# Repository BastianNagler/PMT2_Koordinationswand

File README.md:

# cWall (Interactive Coordination Wall)

cWall is an interactive, reaction-based coordination wall designed as a student project for **PMT2 (Praktikum Messtechnik 2)** during the Summer Semester 2026. 

---

## Game Concept & Play Principle
The cWall is a speed and reaction game where players must trigger randomly illuminated targets as quickly as possible within a 60-second time window.

* **Sequential Progression:** Only one box lights up at a time. The moment it is successfully pressed, the next random target activates instantly.
* **Singleplayer Mode:** The player uses the entire 32-box grid to rack up the highest score possible.
* **Multiplayer Duel Mode:** The playing field is divided into two separate, independent halves (16 boxes each) for head-to-head competition.
* **Integrated Highscores:** The system automatically tracks and saves the top 10 scores persistently.

---

## Key Features
* **ESP32-S3 Control Center:** Runs a FreeRTOS-based firmware.
* **Wireless Web Dashboard:** The ESP32-S3 acts as a Wi-Fi Access Point (SSID: `C-Wall`). By connecting to the network and navigating to `192.168.1.1`, players can view live scores, a countdown timer, game status, and the highscore board in real time. Also the game settings can be adjusted via the web interface and all the logging can be accessed for debugging and performance analysis.
* **Real-time WebSockets:** Utilizes non-blocking WebSocket communication for immediate, bi-directional data transfer between the microcontroller and web browsers.
* **Modular Sensor Boxes:** 32 individual 20x20 cm 3D-printed modular sensor boxes containing internal WS2812b NeoPixel LED strips and TTP223 capacitive touch sensors.
* **Capacitive Touch Detection:** Reliable touch response through a copper-mesh grid embedded into the acrylic faceplates, connected to low-cost, self-contained TTP223 touch chips.
* **Dedicated I/O Expansion:** Employs MCP23018 I/O expanders connected via I²C to handle the high number of digital sensor inputs while conserving ESP32 pins.
* **Robust Power Delivery:** Powered by a 300W (5V/60A) switching power supply, distributed via a star topology to prevent voltage drops when LEDs display full white.
* **Custom PCB Design:** Two-sided component PCB designed using KiCad and manufactured specifically to host the level shifters, I/O expanders, and connector terminals.
* **3D-Printed Enclosures:** All sensor boxes and the main control unit are housed in custom-designed 3D-printed enclosures for durability and aesthetics.

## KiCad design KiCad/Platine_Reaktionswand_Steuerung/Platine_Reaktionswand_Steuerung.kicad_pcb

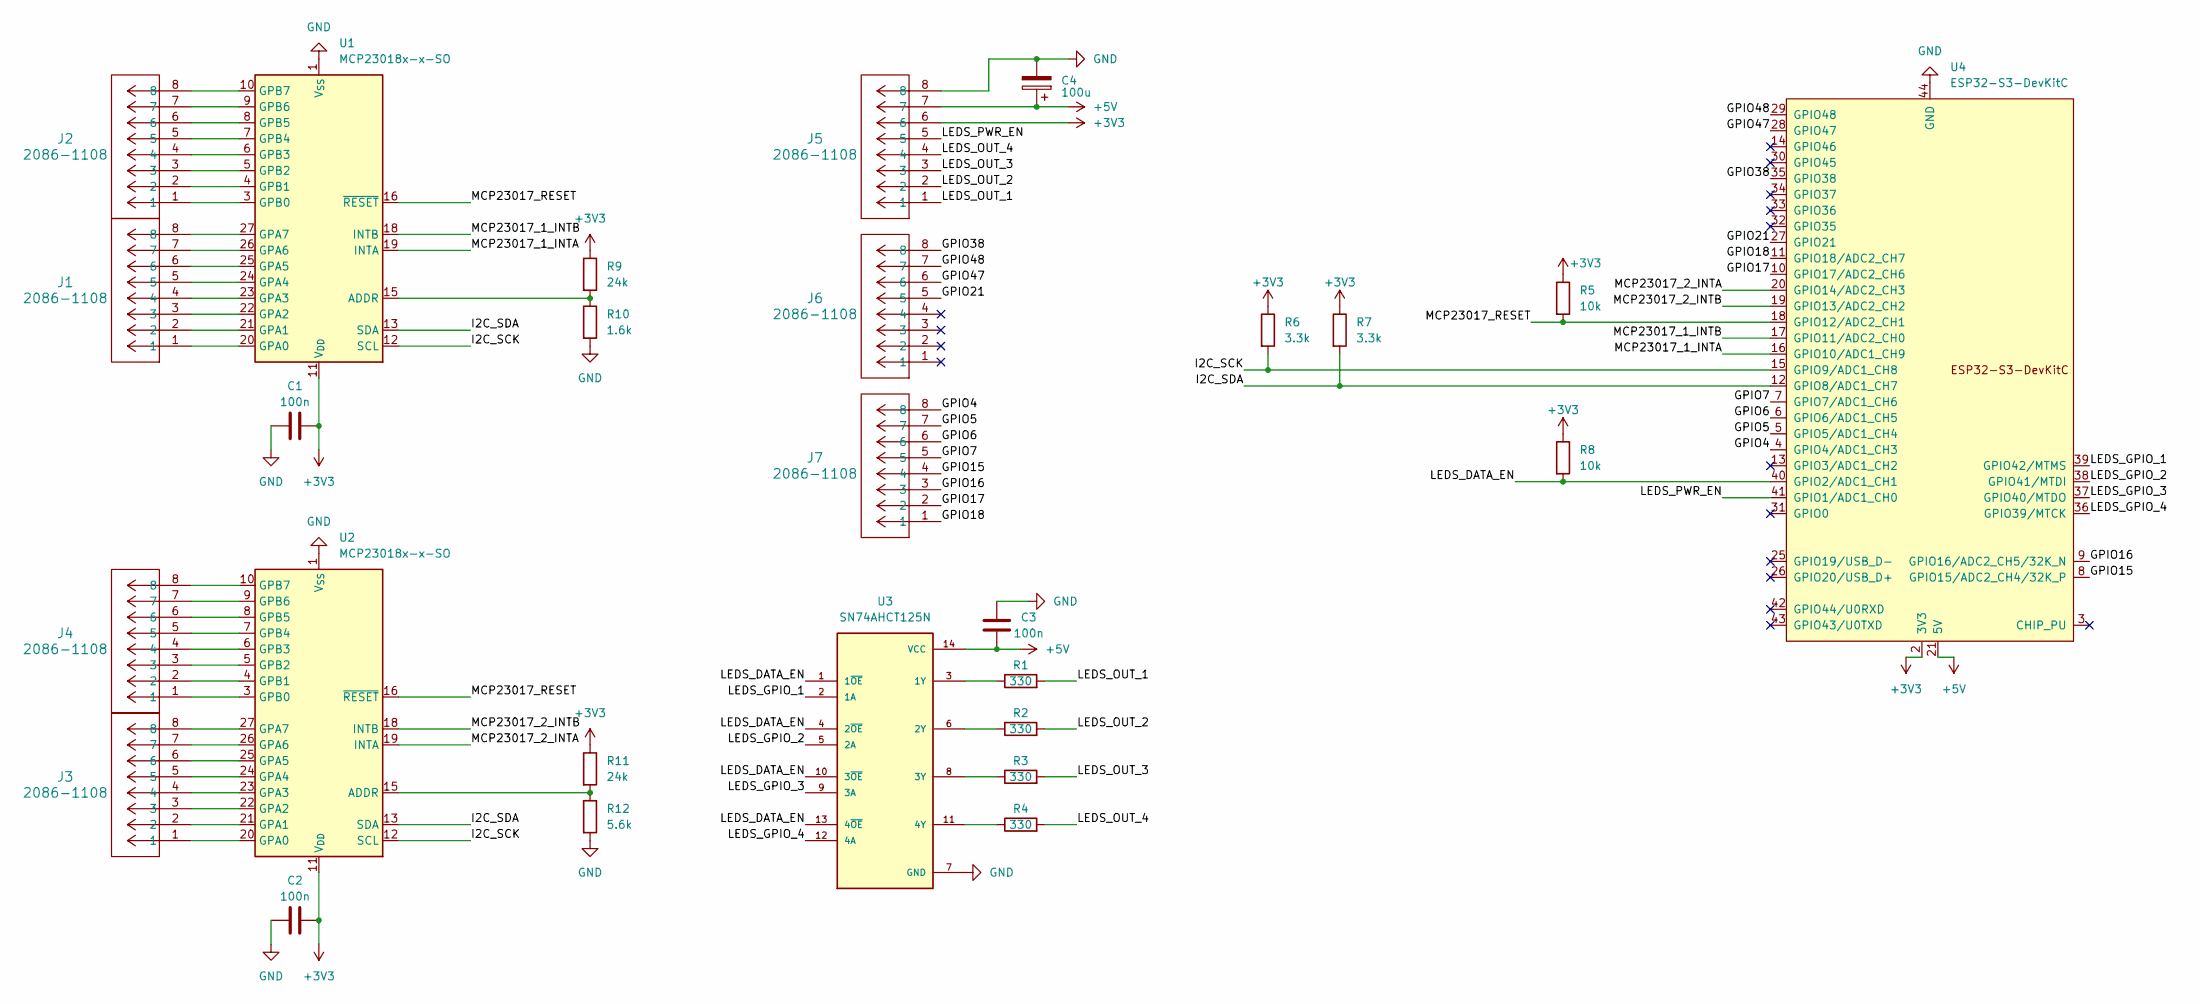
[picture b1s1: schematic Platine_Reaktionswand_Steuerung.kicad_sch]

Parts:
C1, C2, C3: 100n; C_0603_1608Metric_Pad1.08x0.95mm_HandSolder
C4: 100u; CP_Radial_D10.0mm_P5.00mm
J1, J2, J3, J4, J5, J6, J7: 2086-1108; LCSC C3309486
R1, R2, R3, R4: 330; R_0603_1608Metric_Pad0.98x0.95mm_HandSolder
R5, R8: 10k; R_0603_1608Metric_Pad0.98x0.95mm_HandSolder
R6, R7: 3.3k; R_0603_1608Metric_Pad0.98x0.95mm_HandSolder
R9, R11: 24k; R_0603_1608Metric_Pad0.98x0.95mm_HandSolder
R10: 1.6k; R_0603_1608Metric_Pad0.98x0.95mm_HandSolder
R12: 5.6k; R_0603_1608Metric_Pad0.98x0.95mm_HandSolder
U1, U2: MCP23018x-x-SO; SOIC-28W_7.5x17.9mm_P1.27mm
U3: SN74AHCT125N; SN74HCT125N; PARTREV Q; LCSC C354152
U4: ESP32-S3-DevKitC

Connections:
+3V3: C1.1, C2.1, J5.6, R5.1, R6.1, R7.1, R8.1, R9.1, R11.1, U1.11 (V_{DD}), U2.11 (V_{DD}), U4.1 (3V3), U4.2 (3V3)
+5V: C3.2, C4.1, J5.7, U3.14 (VCC), U4.21 (5V)
/GPIO4: J7.8, U4.4 (GPIO4/ADC1_CH3)
/GPIO5: J7.7, U4.5 (GPIO5/ADC1_CH4)
/GPIO6: J7.6, U4.6 (GPIO6/ADC1_CH5)
/GPIO7: J7.5, U4.7 (GPIO7/ADC1_CH6)
/GPIO15: J7.4, U4.8 (GPIO15/ADC2_CH4/32K_P)
/GPIO16: J7.3, U4.9 (GPIO16/ADC2_CH5/32K_N)
/GPIO17: J7.2, U4.10 (GPIO17/ADC2_CH6)
/GPIO18: J7.1, U4.11 (GPIO18/ADC2_CH7)
/GPIO21: J6.5, U4.27 (GPIO21)
/GPIO38: J6.8, U4.35 (GPIO38)
/GPIO47: J6.6, U4.28 (GPIO47)
/GPIO48: J6.7, U4.29 (GPIO48)
/I2C_SCK: R6.2, U1.12 (SCL), U2.12 (SCL), U4.15 (GPIO9/ADC1_CH8)
/I2C_SDA: R7.2, U1.13 (SDA), U2.13 (SDA), U4.12 (GPIO8/ADC1_CH7)
/LEDS_DATA_EN: R8.2, U3.1 (1~OE), U3.4 (2~OE), U3.10 (3~OE), U3.13 (4~OE), U4.40 (GPIO2/ADC1_CH1)
/LEDS_GPIO_1: U3.2 (1A), U4.39 (GPIO42/MTMS)
/LEDS_GPIO_2: U3.5 (2A), U4.38 (GPIO41/MTDI)
/LEDS_GPIO_3: U3.9 (3A), U4.37 (GPIO40/MTDO)
/LEDS_GPIO_4: U3.12 (4A), U4.36 (GPIO39/MTCK)
/LEDS_OUT_1: J5.1, R1.2
/LEDS_OUT_2: J5.2, R2.2
/LEDS_OUT_3: J5.3, R3.2
/LEDS_OUT_4: J5.4, R4.2
/LEDS_PWR_EN: J5.5, U4.41 (GPIO1/ADC1_CH0)
/MCP23017_1_INTA: U1.19 (INTA), U4.16 (GPIO10/ADC1_CH9)
/MCP23017_1_INTB: U1.18 (INTB), U4.17 (GPIO11/ADC2_CH0)
/MCP23017_2_INTA: U2.19 (INTA), U4.20 (GPIO14/ADC2_CH3)
/MCP23017_2_INTB: U2.18 (INTB), U4.19 (GPIO13/ADC2_CH2)
/MCP23017_RESET: R5.2, U1.16 (~RESET), U2.16 (~RESET), U4.18 (GPIO12/ADC2_CH1)
GND: C1.2, C2.2, C3.1, C4.2, J5.8, R10.2, R12.2, U1.1 (V_{SS}), U2.1 (V_{SS}), U3.7 (GND), U4.22 (GND), U4.23 (GND), U4.24 (GND), U4.44 (GND)
unnamed: R9.2, R10.1, U1.15 (ADDR)
unnamed: J1.1, U1.20 (GPA0)
unnamed: J1.2, U1.21 (GPA1)
unnamed: J1.3, U1.22 (GPA2)
unnamed: J1.4, U1.23 (GPA3)
unnamed: J1.5, U1.24 (GPA4)
unnamed: J1.6, U1.25 (GPA5)
unnamed: J1.7, U1.26 (GPA6)
unnamed: J1.8, U1.27 (GPA7)
unnamed: J2.1, U1.3 (GPB0)
unnamed: J2.2, U1.4 (GPB1)
unnamed: J2.3, U1.5 (GPB2)
unnamed: J2.4, U1.6 (GPB3)
unnamed: J2.5, U1.7 (GPB4)
unnamed: J2.6, U1.8 (GPB5)
unnamed: J2.7, U1.9 (GPB6)
unnamed: J2.8, U1.10 (GPB7)
unnamed: R11.2, R12.1, U2.15 (ADDR)
unnamed: J3.1, U2.20 (GPA0)
unnamed: J3.2, U2.21 (GPA1)
unnamed: J3.3, U2.22 (GPA2)
unnamed: J3.4, U2.23 (GPA3)
unnamed: J3.5, U2.24 (GPA4)
unnamed: J3.6, U2.25 (GPA5)
unnamed: J3.7, U2.26 (GPA6)
unnamed: J3.8, U2.27 (GPA7)
unnamed: J4.1, U2.3 (GPB0)
unnamed: J4.2, U2.4 (GPB1)
unnamed: J4.3, U2.5 (GPB2)
unnamed: J4.4, U2.6 (GPB3)
unnamed: J4.5, U2.7 (GPB4)
unnamed: J4.6, U2.8 (GPB5)
unnamed: J4.7, U2.9 (GPB6)
unnamed: J4.8, U2.10 (GPB7)
unnamed: R1.1, U3.3 (1Y)
unnamed: R2.1, U3.6 (2Y)
unnamed: R3.1, U3.8 (3Y)
unnamed: R4.1, U3.11 (4Y)

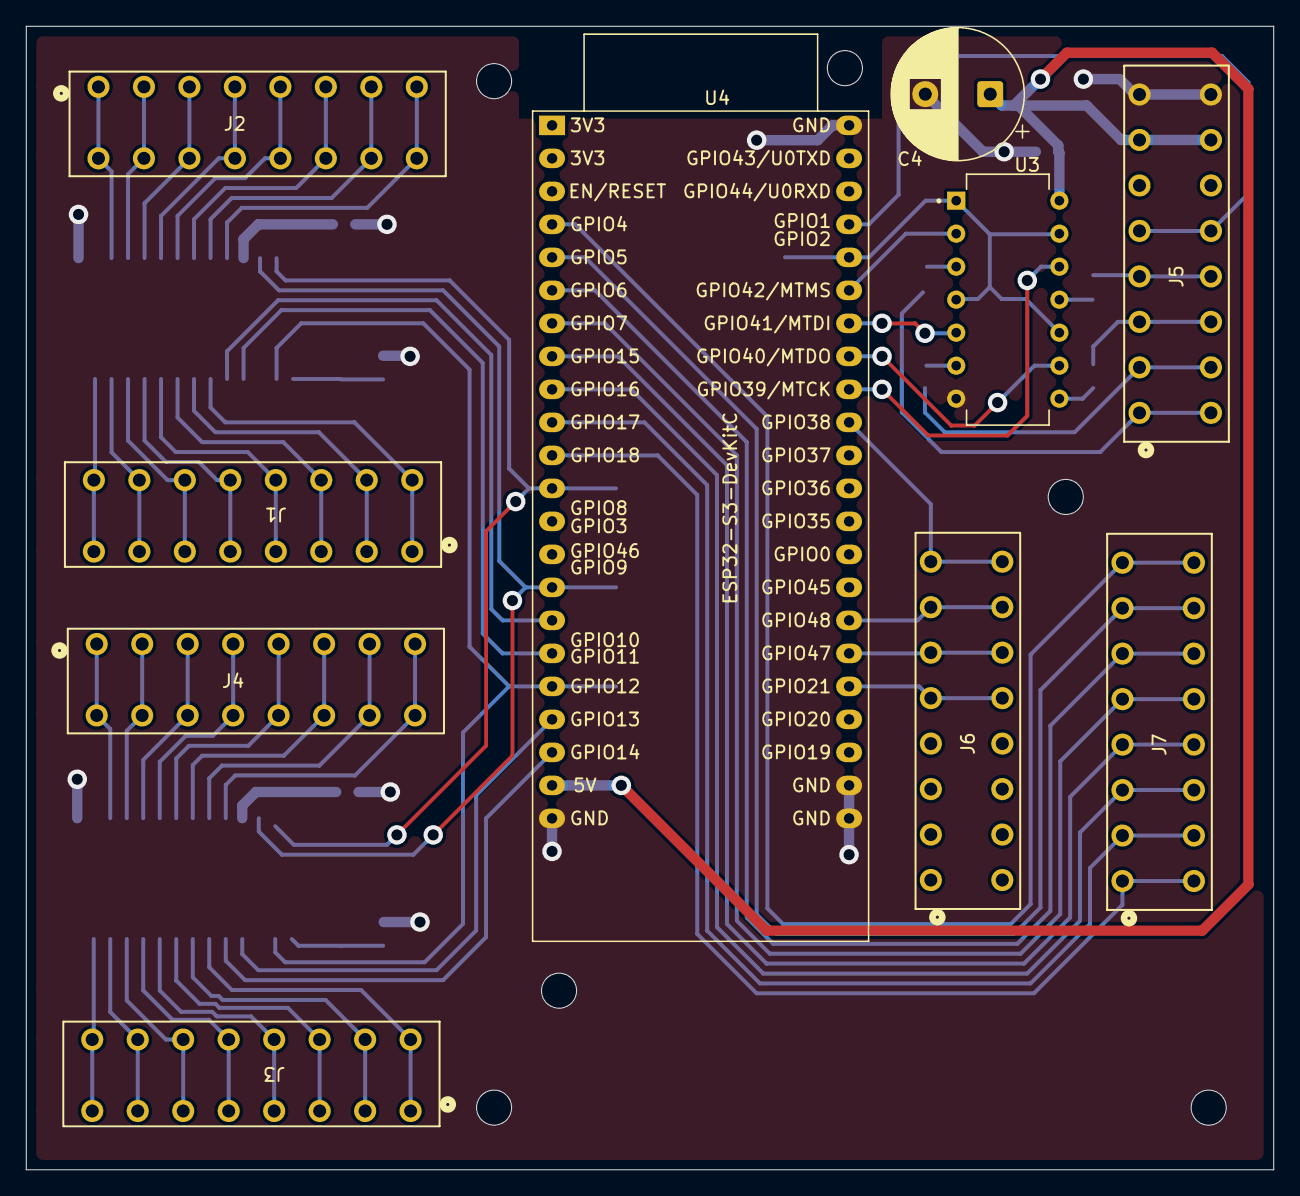
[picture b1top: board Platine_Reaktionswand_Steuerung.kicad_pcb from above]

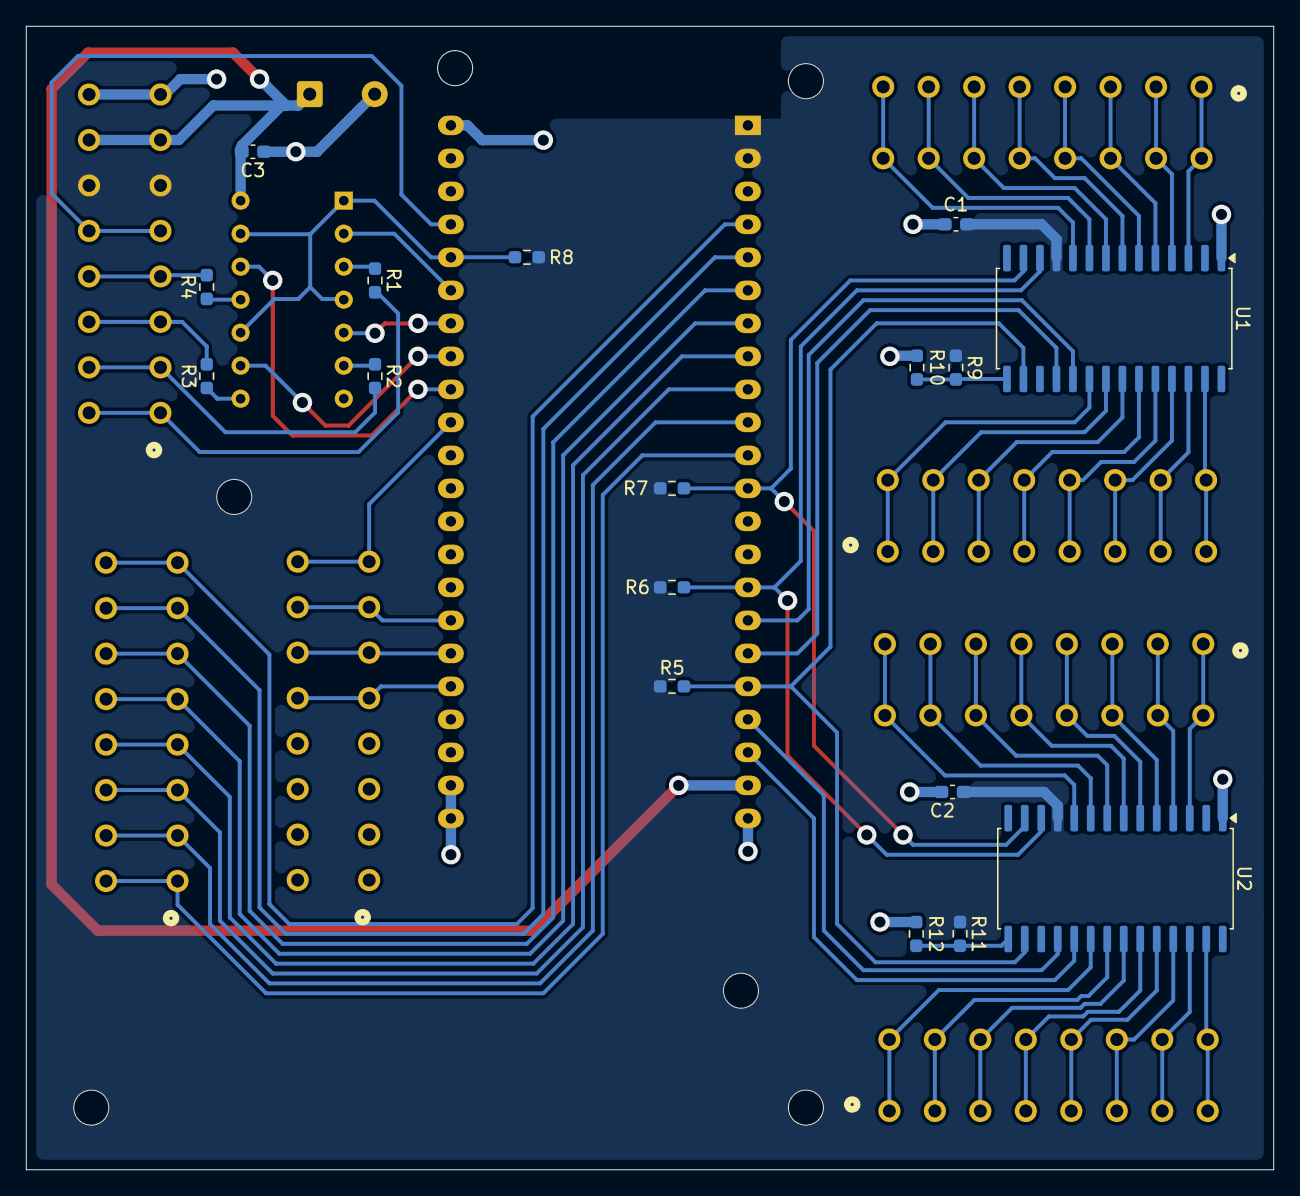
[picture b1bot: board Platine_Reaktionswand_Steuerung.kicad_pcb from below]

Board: 2 copper layers, 96.0 x 88.0 mm, 27 parts (17 on the bottom side), 70 nets.

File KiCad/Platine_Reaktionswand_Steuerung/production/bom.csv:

Designator,Footprint,Quantity,Value,LCSC Part #
"C1, C2, C3",0603,3,100n,
C4,CP_Radial_D10.0mm_P5.00mm,1,100u,
"J1, J2, J3, J4, J5, J6, J7",2086-1108,7,2086-1108,C3309486
"R1, R2, R3, R4",0603,4,330,
R10,0603,1,1.6k,
"R11, R9",0603,2,24k,
R12,0603,1,5.6k,
"R5, R8",0603,2,10k,
"R6, R7",0603,2,3.3k,
"U1, U2",SOIC-28W_7.5x17.9mm_P1.27mm,2,MCP23018x-x-SO,
U3,SN74HCT125N,1,SN74AHCT125N,C354152
U4,ESP32-S3-DevKitC,1,ESP32-S3-DevKitC,

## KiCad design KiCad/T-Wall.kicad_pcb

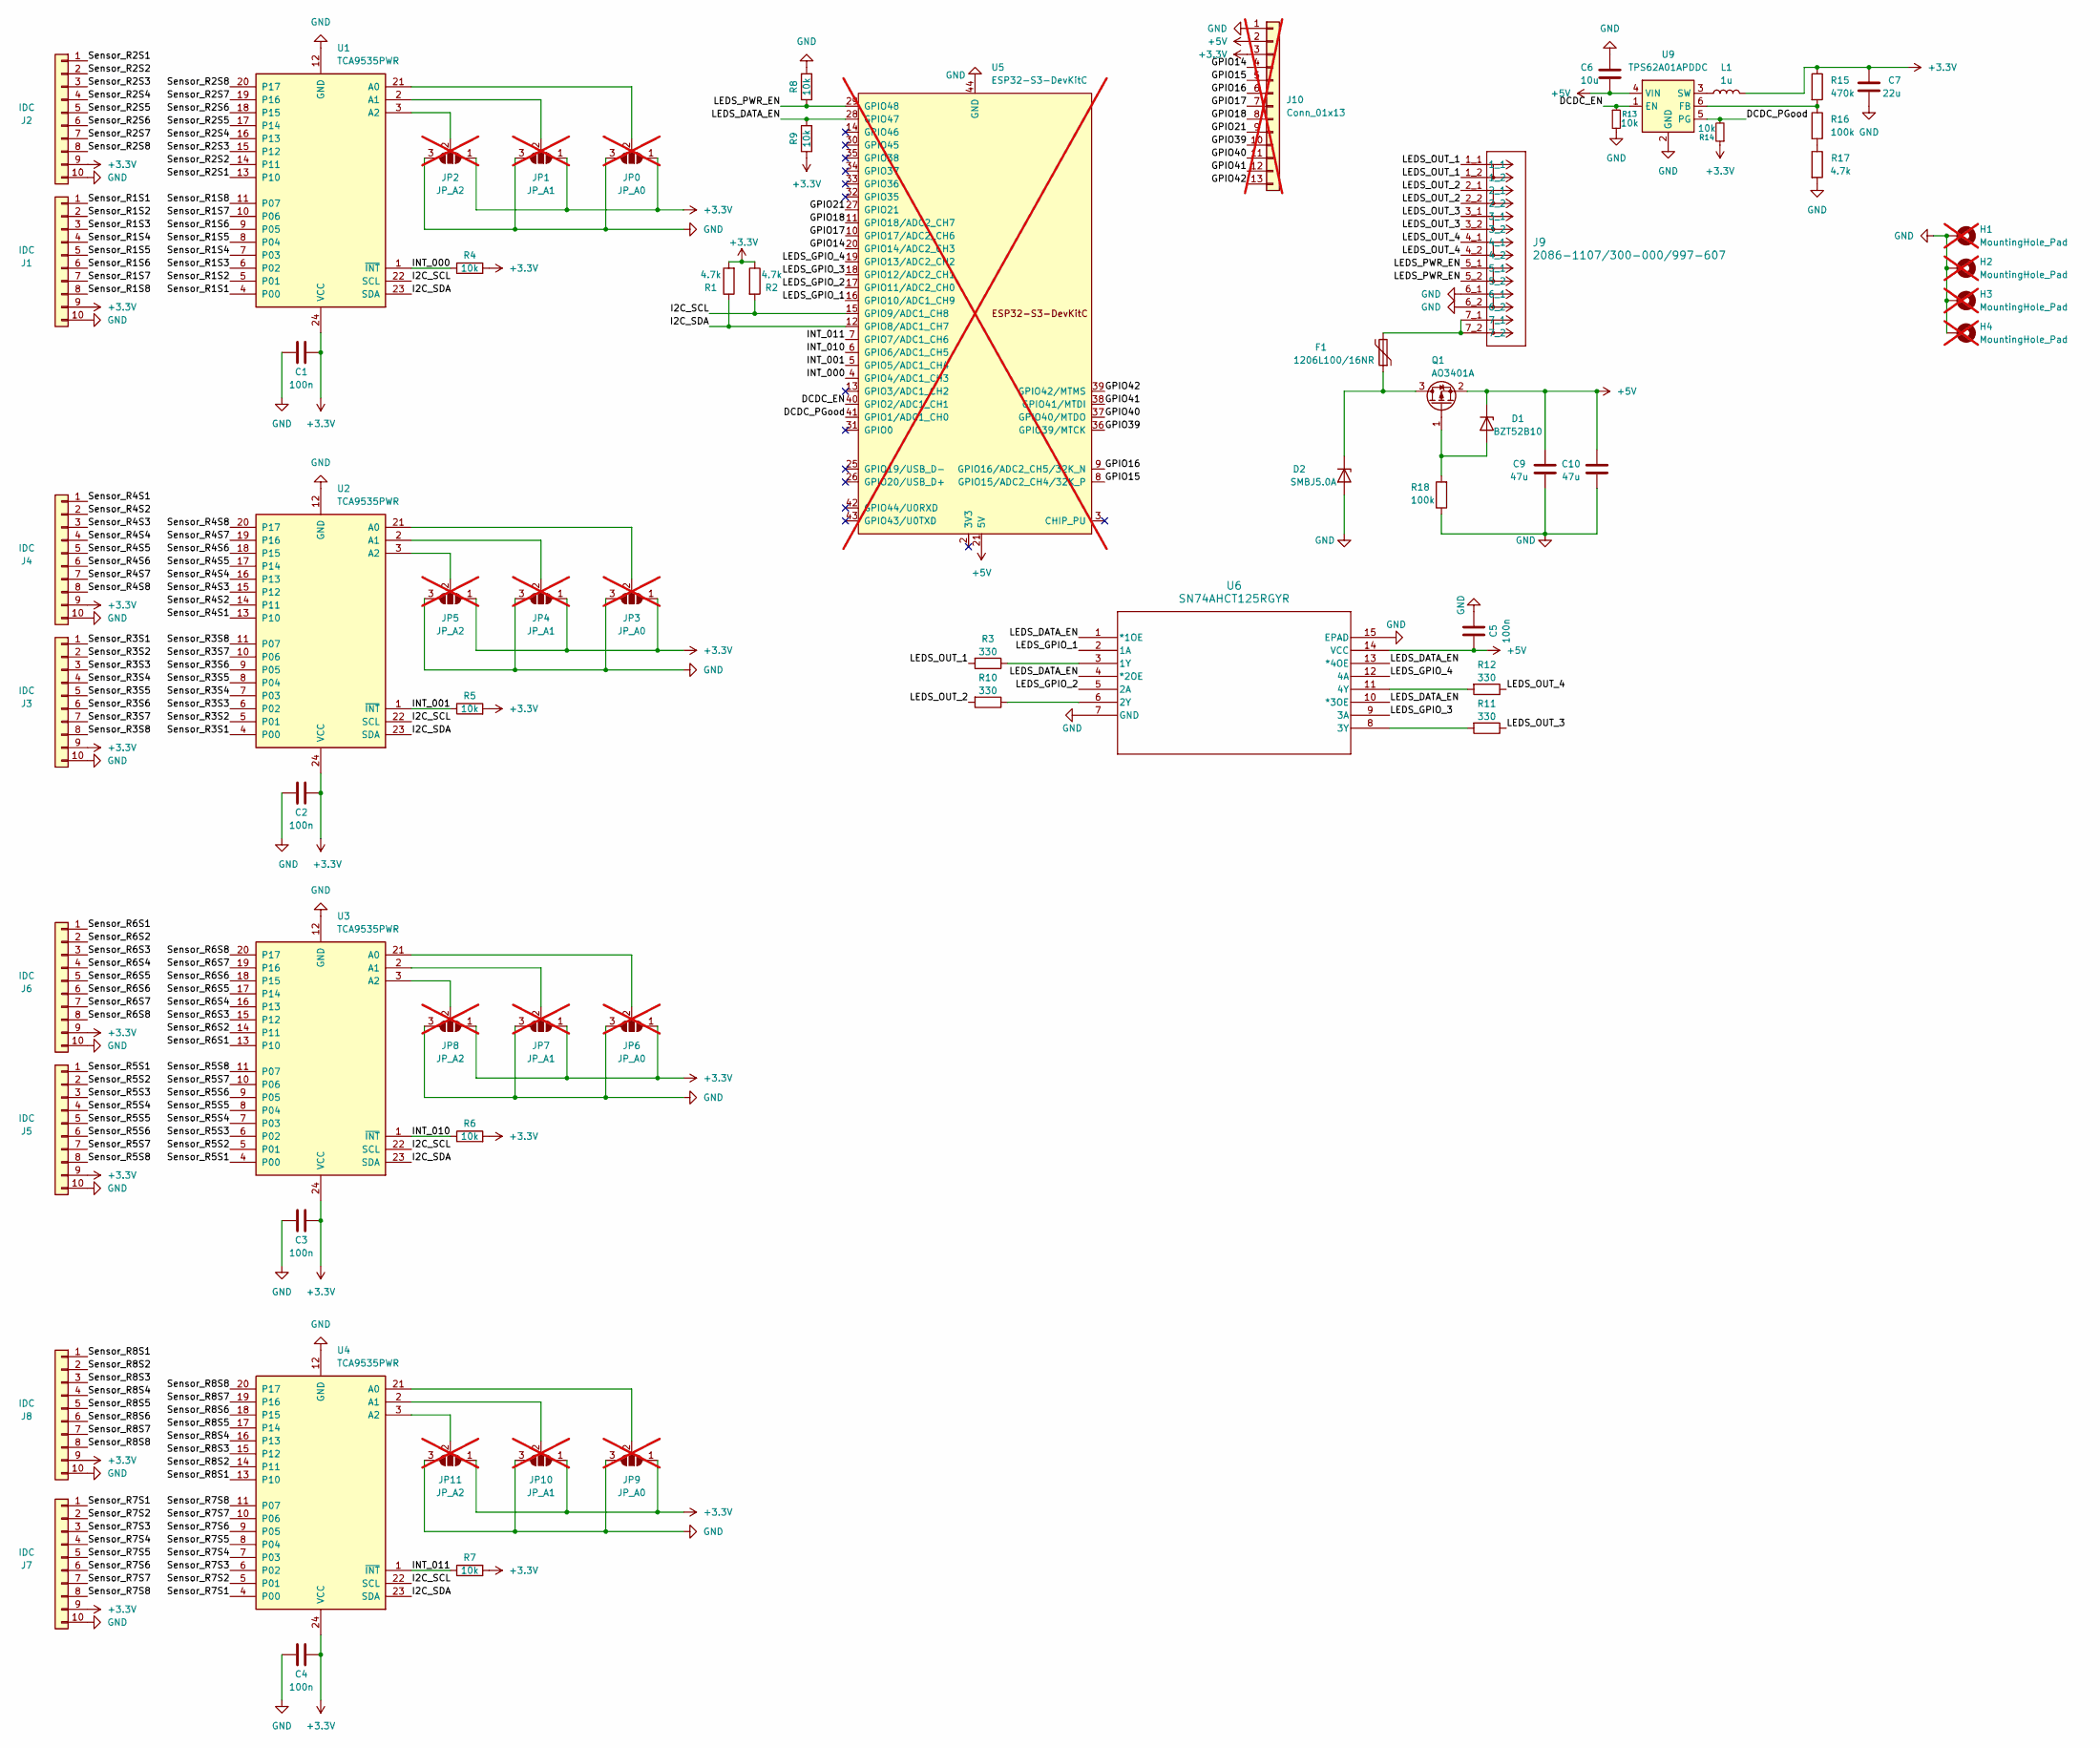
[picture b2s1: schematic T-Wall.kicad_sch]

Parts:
C1, C2, C3, C4, C5: 100n; C_0603_1608Metric_Pad1.08x0.95mm_HandSolder; LCSC C14663
C6: 10u; C_1206_3216Metric_Pad1.33x1.80mm_HandSolder; LCSC C13585
C7: 22u; C_1206_3216Metric_Pad1.33x1.80mm_HandSolder; LCSC C12891
C9, C10: 47u; C_1206_3216Metric_Pad1.33x1.80mm_HandSolder; LCSC C96123
D1: BZT52B10; D_SOD-123F; LCSC C22395568
D2: SMBJ5.0A; D_SMB_Handsoldering; LCSC C19077558
F1: 1206L100/16NR; Fuse_1206_3216Metric_Pad1.42x1.75mm_HandSolder; LCSC C7542956
H1, H2, H3, H4: MountingHole_Pad; MountingHole_3.2mm_M3_Pad_Via; not fitted
J1, J2, J3, J4, J5, J6, J7, J8: IDC; IDC-Header_2x05_P2.54mm_Vertical; LCSC C429962
J9: 2086-1107/300-000/997-607; 2086-1107_300-000_997-607; LCSC C3309486
J10: Conn_01x13; PinHeader_1x13_P2.54mm_Vertical; not fitted
JP0, JP3, JP6, JP9: JP_A0; SolderJumper-3_P1.3mm_Open_RoundedPad1.0x1.5mm; not fitted
JP1, JP4, JP7, JP10: JP_A1; SolderJumper-3_P1.3mm_Open_RoundedPad1.0x1.5mm; not fitted
JP2, JP5, JP8, JP11: JP_A2; SolderJumper-3_P1.3mm_Open_RoundedPad1.0x1.5mm; not fitted
L1: 1u; L_0805_2012Metric_Pad1.05x1.20mm_HandSolder; LCSC C6364732
Q1: AO3401A; SOT-23; LCSC C15127
R1, R2, R17: 4.7k; R_0603_1608Metric_Pad0.98x0.95mm_HandSolder; LCSC C23162
R3, R10, R11, R12: 330; R_0603_1608Metric_Pad0.98x0.95mm_HandSolder; LCSC C23138
R4, R5, R6, R7, R8, R9, R13, R14: 10k; R_0603_1608Metric_Pad0.98x0.95mm_HandSolder; LCSC C25804
R15: 470k; R_0603_1608Metric_Pad0.98x0.95mm_HandSolder; LCSC C23178
R16, R18: 100k; R_0603_1608Metric_Pad0.98x0.95mm_HandSolder; LCSC C25803
U1, U2, U3, U4: TCA9535PWR; TSSOP-24_4.4x7.8mm_P0.65mm; LCSC C130204
U5: ESP32-S3-DevKitC; not fitted
U6: SN74AHCT125RGYR; LCSC C2675532
U9: TPS62A01APDDC; SOT-23-6; LCSC C41730179

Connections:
+3.3V: C1.1, C2.1, C3.1, C4.1, C7.2, J1.9, J2.9, J3.9, J4.9, J5.9, J6.9, J7.9, J8.9, J10.3, JP0.1 (A), JP1.1 (A), JP2.1 (A), JP3.1 (A), JP4.1 (A), JP5.1 (A), JP6.1 (A), JP7.1 (A), JP8.1 (A), JP9.1 (A), JP10.1 (A), JP11.1 (A), L1.2, R1.2, R2.1, R4.2, R5.2, R6.2, R7.2, R9.1, R14.1, R15.1, U1.24 (VCC), U2.24 (VCC), U3.24 (VCC), U4.24 (VCC)
+5V: C5.2, C6.2, C9.2, C10.2, D1.1 (K), J10.2, Q1.2 (S), U5.21 (5V), U6.14 (VCC), U9.4 (VIN)
/DCDC_EN: R13.1, U5.40 (GPIO2/ADC1_CH1), U9.1 (EN)
/DCDC_PGood: R14.2, U5.41 (GPIO1/ADC1_CH0), U9.5 (PG)
/GPIO14: J10.4, U5.20 (GPIO14/ADC2_CH3)
/GPIO15: J10.5, U5.8 (GPIO15/ADC2_CH4/32K_P)
/GPIO16: J10.6, U5.9 (GPIO16/ADC2_CH5/32K_N)
/GPIO17: J10.7, U5.10 (GPIO17/ADC2_CH6)
/GPIO18: J10.8, U5.11 (GPIO18/ADC2_CH7)
/GPIO21: J10.9, U5.27 (GPIO21)
/GPIO39: J10.10, U5.36 (GPIO39/MTCK)
/GPIO40: J10.11, U5.37 (GPIO40/MTDO)
/GPIO41: J10.12, U5.38 (GPIO41/MTDI)
/GPIO42: J10.13, U5.39 (GPIO42/MTMS)
/I2C_SCL: R2.2, U1.22 (SCL), U2.22 (SCL), U3.22 (SCL), U4.22 (SCL), U5.15 (GPIO9/ADC1_CH8)
/I2C_SDA: R1.1, U1.23 (SDA), U2.23 (SDA), U3.23 (SDA), U4.23 (SDA), U5.12 (GPIO8/ADC1_CH7)
/INT_000: R4.1, U1.1 (~INT), U5.4 (GPIO4/ADC1_CH3)
/INT_001: R5.1, U2.1 (~INT), U5.5 (GPIO5/ADC1_CH4)
/INT_010: R6.1, U3.1 (~INT), U5.6 (GPIO6/ADC1_CH5)
/INT_011: R7.1, U4.1 (~INT), U5.7 (GPIO7/ADC1_CH6)
/LEDS_DATA_EN: R9.2, U5.28 (GPIO47), U6.1 (*1OE), U6.4 (*2OE), U6.10 (*3OE), U6.13 (*4OE)
/LEDS_GPIO_1: U5.16 (GPIO10/ADC1_CH9), U6.2 (1A)
/LEDS_GPIO_2: U5.17 (GPIO11/ADC2_CH0), U6.5 (2A)
/LEDS_GPIO_3: U5.18 (GPIO12/ADC2_CH1), U6.9 (3A)
/LEDS_GPIO_4: U5.19 (GPIO13/ADC2_CH2), U6.12 (4A)
/LEDS_OUT_1: J9.1_1, J9.1_2, R3.2
/LEDS_OUT_2: J9.2_1, J9.2_2, R10.2
/LEDS_OUT_3: J9.3_1, J9.3_2, R11.1
/LEDS_OUT_4: J9.4_1, J9.4_2, R12.1
/LEDS_PWR_EN: J9.5_1, J9.5_2, R8.1, U5.29 (GPIO48)
/Sensor_R1S1: J1.1, U1.4 (P00)
/Sensor_R1S2: J1.2, U1.5 (P01)
/Sensor_R1S3: J1.3, U1.6 (P02)
/Sensor_R1S4: J1.4, U1.7 (P03)
/Sensor_R1S5: J1.5, U1.8 (P04)
/Sensor_R1S6: J1.6, U1.9 (P05)
/Sensor_R1S7: J1.7, U1.10 (P06)
/Sensor_R1S8: J1.8, U1.11 (P07)
/Sensor_R2S1: J2.1, U1.13 (P10)
/Sensor_R2S2: J2.2, U1.14 (P11)
/Sensor_R2S3: J2.3, U1.15 (P12)
/Sensor_R2S4: J2.4, U1.16 (P13)
/Sensor_R2S5: J2.5, U1.17 (P14)
/Sensor_R2S6: J2.6, U1.18 (P15)
/Sensor_R2S7: J2.7, U1.19 (P16)
/Sensor_R2S8: J2.8, U1.20 (P17)
/Sensor_R3S1: J3.1, U2.4 (P00)
/Sensor_R3S2: J3.2, U2.5 (P01)
/Sensor_R3S3: J3.3, U2.6 (P02)
/Sensor_R3S4: J3.4, U2.7 (P03)
/Sensor_R3S5: J3.5, U2.8 (P04)
/Sensor_R3S6: J3.6, U2.9 (P05)
/Sensor_R3S7: J3.7, U2.10 (P06)
/Sensor_R3S8: J3.8, U2.11 (P07)
/Sensor_R4S1: J4.1, U2.13 (P10)
/Sensor_R4S2: J4.2, U2.14 (P11)
/Sensor_R4S3: J4.3, U2.15 (P12)
/Sensor_R4S4: J4.4, U2.16 (P13)
/Sensor_R4S5: J4.5, U2.17 (P14)
/Sensor_R4S6: J4.6, U2.18 (P15)
/Sensor_R4S7: J4.7, U2.19 (P16)
/Sensor_R4S8: J4.8, U2.20 (P17)
/Sensor_R5S1: J5.1, U3.4 (P00)
/Sensor_R5S2: J5.2, U3.5 (P01)
/Sensor_R5S3: J5.3, U3.6 (P02)
/Sensor_R5S4: J5.4, U3.7 (P03)
/Sensor_R5S5: J5.5, U3.8 (P04)
/Sensor_R5S6: J5.6, U3.9 (P05)
/Sensor_R5S7: J5.7, U3.10 (P06)
/Sensor_R5S8: J5.8, U3.11 (P07)
/Sensor_R6S1: J6.1, U3.13 (P10)
/Sensor_R6S2: J6.2, U3.14 (P11)
/Sensor_R6S3: J6.3, U3.15 (P12)
/Sensor_R6S4: J6.4, U3.16 (P13)
/Sensor_R6S5: J6.5, U3.17 (P14)
/Sensor_R6S6: J6.6, U3.18 (P15)
/Sensor_R6S7: J6.7, U3.19 (P16)
/Sensor_R6S8: J6.8, U3.20 (P17)
/Sensor_R7S1: J7.1, U4.4 (P00)
/Sensor_R7S2: J7.2, U4.5 (P01)
/Sensor_R7S3: J7.3, U4.6 (P02)
/Sensor_R7S4: J7.4, U4.7 (P03)
/Sensor_R7S5: J7.5, U4.8 (P04)
/Sensor_R7S6: J7.6, U4.9 (P05)
/Sensor_R7S7: J7.7, U4.10 (P06)
/Sensor_R7S8: J7.8, U4.11 (P07)
/Sensor_R8S1: J8.1, U4.13 (P10)
/Sensor_R8S2: J8.2, U4.14 (P11)
/Sensor_R8S3: J8.3, U4.15 (P12)
/Sensor_R8S4: J8.4, U4.16 (P13)
/Sensor_R8S5: J8.5, U4.17 (P14)
/Sensor_R8S6: J8.6, U4.18 (P15)
/Sensor_R8S7: J8.7, U4.19 (P16)
/Sensor_R8S8: J8.8, U4.20 (P17)
GND: C1.2, C2.2, C3.2, C4.2, C5.1, C6.1, C7.1, C9.1, C10.1, D2.2 (A), H1.1 (1_1), H2.1 (1_1), H3.1 (1_1), H4.1 (1_1), J1.10, J2.10, J3.10, J4.10, J5.10, J6.10, J7.10, J8.10, J9.6_1, J9.6_2, J10.1, JP0.3 (B), JP1.3 (B), JP2.3 (B), JP3.3 (B), JP4.3 (B), JP5.3 (B), JP6.3 (B), JP7.3 (B), JP8.3 (B), JP9.3 (B), JP10.3 (B), JP11.3 (B), R8.2, R13.2, R17.2, R18.1, U1.12 (GND), U2.12 (GND), U3.12 (GND), U4.12 (GND), U5.22 (GND), U5.23 (GND), U5.24 (GND), U5.44 (GND), U6.7 (GND), U6.15 (EPAD), U9.2 (GND)
unnamed: D1.2 (A), Q1.1 (G), R18.2
unnamed: D2.1 (K), F1.1, Q1.3 (D)
unnamed: F1.2, J9.7_1, J9.7_2
unnamed: JP0.2 (C), U1.21 (A0)
unnamed: JP1.2 (C), U1.2 (A1)
unnamed: JP2.2 (C), U1.3 (A2)
unnamed: JP3.2 (C), U2.21 (A0)
unnamed: JP4.2 (C), U2.2 (A1)
unnamed: JP5.2 (C), U2.3 (A2)
unnamed: JP6.2 (C), U3.21 (A0)
unnamed: JP7.2 (C), U3.2 (A1)
unnamed: JP8.2 (C), U3.3 (A2)
unnamed: JP9.2 (C), U4.21 (A0)
unnamed: JP10.2 (C), U4.2 (A1)
unnamed: JP11.2 (C), U4.3 (A2)
unnamed: R16.2, R17.1
unnamed: R3.1, U6.3 (1Y)
unnamed: R10.1, U6.6 (2Y)
unnamed: R11.2, U6.8 (3Y)
unnamed: R12.2, U6.11 (4Y)
unnamed: R15.2, R16.1, U9.6 (FB)
unnamed: L1.1, U9.3 (SW)

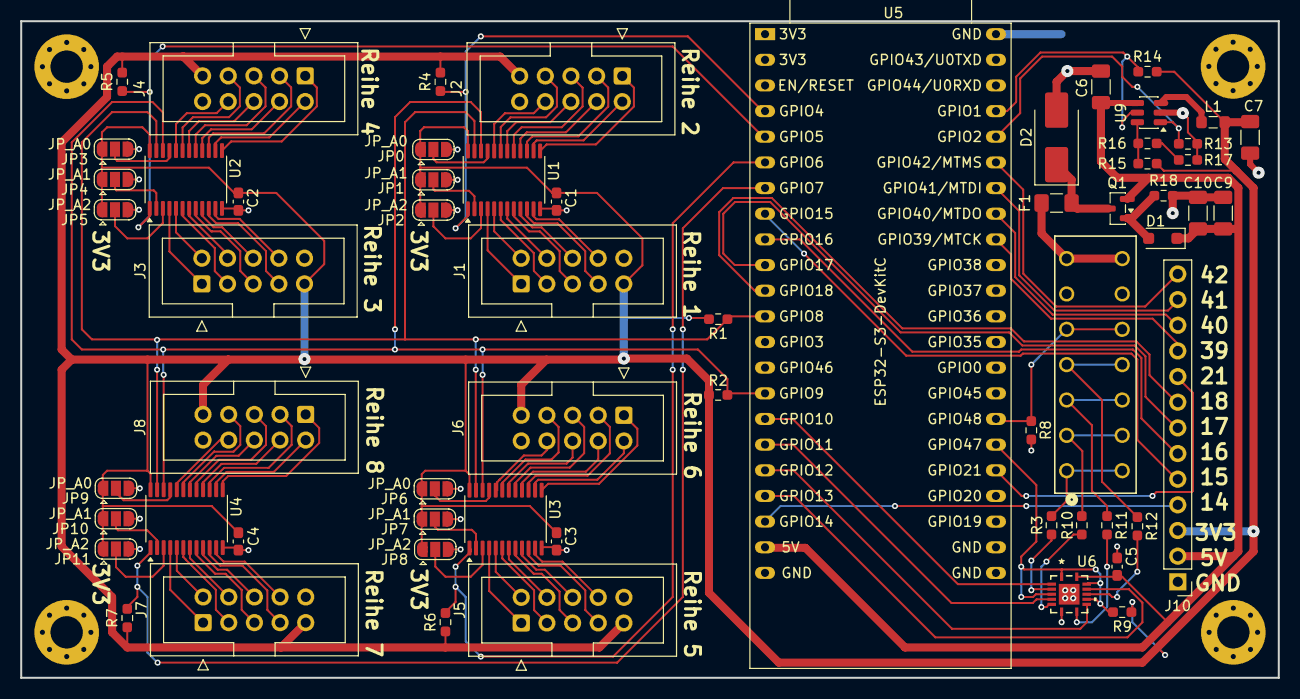
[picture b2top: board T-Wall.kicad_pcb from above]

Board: 2 copper layers, 124.5 x 65.0 mm, 65 parts (0 on the bottom side), 117 nets.

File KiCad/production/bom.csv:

Designator,Footprint,Quantity,Value,LCSC Part #
"C1, C2, C3, C4, C5",0603,5,100n,C14663
"C10, C9",1206,2,47u,C96123
C6,1206,1,10u,C13585
C7,1206,1,22u,C12891
D1,D_SOD-123F,1,BZT52B10,C22395568
D2,D_SMB_Handsoldering,1,SMBJ5.0A,C19077558
F1,1206,1,1206L100/16NR,C7542956
"J1, J2, J3, J4, J5, J6, J7, J8",IDC-Header_2x05_P2.54mm_Vertical,8,IDC,C429962
J9,2086-1107_300-000_997-607,1,2086-1107/300-000/997-607,C3309486
L1,0805,1,1u,C6364732
Q1,SOT-23,1,AO3401A,C15127
"R1, R17, R2",0603,3,4.7k,C23162
"R10, R11, R12, R3",0603,4,330,C23138
"R13, R14, R4, R5, R6, R7, R8, R9",0603,8,10k,C25804
R15,0603,1,470k,C23178
"R16, R18",0603,2,100k,C25803
"U1, U2, U3, U4",TSSOP-24_4.4x7.8mm_P0.65mm,4,TCA9535PWR,C130204
U6,SN74AHCT125RGYR,1,SN74AHCT125RGYR,C2675532
U9,SOT-23-6,1,TPS62A01APDDC,C41730179

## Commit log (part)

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2026-03-06 Added support for Fields in LED_Driver and added RGB_Color class
2026-03-06 Changed TCA9555_Driver to be universally usable
2026-03-09 minor QOL changes
2026-03-09 fixed correct init
2026-03-09 Added working Project for 1st Prototype
2026-03-09 updated LED_Driver to use allocated array instead of std::vector
2026-03-11 Fixed minor issue in LED_Driver (wrong constant used in set_led_in_field)
2026-03-11 EOD 11.03
2026-03-12 PCB Revision 1
2026-03-12 PCB Revision 2
2026-03-13 EOD 1303
2026-03-13 added KiCad libraries to repo
2026-03-16 changed KiCad libraries to project-specific libraries
2026-03-16 added ESP32 Software to repo
2026-03-17 just some BWL things...
2026-03-18 Finished BWL-rebuild
2026-03-29 added 3D-print files for a single box
2026-03-29 added cmake-build directory to gitignore
2026-03-29 fixed correct define for FastLED to use I2S
2026-03-29 fixed false fix for FastLED to use I2S (testing is important)
2026-03-29 added 100 nF capacitor for the level-shifter
2026-03-29 PCB QOL: changed sizes to 0603 and moved vias away from pads
2026-03-30 irgendwas schaltplan
2026-03-30 PCB: routed unused GPIOs to Pins
2026-04-06 deleted config for non-WS2812b LEDs
2026-04-07 PCB: corrected WAGO footprint
2026-04-09 PCB: added fuse and reverse-polarity-protection
2026-04-09 changed colors to cyan and yellow
2026-04-11 PCB: overvoltage-protection and optimized routing
2026-04-11 PCB: upgraded KiCad to 10.0.1
2026-04-12 PCB: finished for purchase at JLCPCB
2026-04-16 added MCP23017 support to ESP program
2026-04-18 cleared warning for MCP23017 driver
2026-04-19 added game Logic in main (todo: new class and file)
2026-04-19 added color GRAY
2026-04-19 added led-driver as a HAL
2026-04-19 added bool ispressed(intdex)
2026-04-19 changed pin-config for use with test-breadboard
2026-04-20 changed startgame()
2026-04-20 changed game logic (State machine)
2026-04-20 added multiplayer logic
2026-04-20 gamelogic in TwallGame
2026-04-20 deleted help_blink
2026-04-20 added pragma once
2026-04-20 changed Field logic in left/right
2026-04-20 deleted color definition in main
2026-04-20 added highscores (permanent)
2026-04-20 same field can be generated (commented do, while)
2026-04-23 added the IO_Expander container-class as HAL
2026-04-27 Added final STLs and the Bambu Studio Project
2026-04-30 changed to 4 Boxes
2026-04-30 cchanged config IO Expander
2026-04-30 same fields are forbidden
2026-05-03 final Bambu Studio project file with best results
2026-05-03 PCB: changed PCB from JLCPCB-version to OTH-version
2026-05-04 changed config to work with PCB
2026-05-04 fixed bug: retry search for IO-Expander when it isnt found
2026-05-05 fixed issue with USB-Serial not working
2026-05-05 added the LED_DATA_EN pin functionality
2026-05-20 changed gameend
2026-05-24 changed multplayer end (and color config)
2026-05-27 merged webhost
2026-05-27 minor changes for stability and added ripple-animation
2026-05-27 added watchdog-timer
2026-05-27 implemented FreeRTOS architecture
2026-05-28 fixed task_watchdog issue and stack overflow for the Input-Task
2026-05-28 optimized heartbeat.update to only update the OnBoard-LED
2026-05-28 fixed main to working RTOS
2026-05-28 changed MCP23018.init() to not try multiple times for watchdog to work
2026-05-28 deleted watchdogTask remains
2026-05-28 refactored TwallGame and added a HighscoreManager
2026-05-28 changed strncpy to strlcpy
2026-05-30 optimized heartbeat.init() with quicker show-function
2026-06-02 updated Wifi Interface with static IP
2026-06-02 updated name from tWall to cWall
2026-06-03 final config file
2026-06-03 change Heartbeat-LED to use bitbanging to not run out of Hardware-Drivers
2026-06-03 fixed webserver bug gamestate
2026-06-03 added box 16 read and hopefully fixed buggy leds
2026-06-03 fixed wrong color being shown after the ripple animation
2026-06-03 reenabled box 16
2026-06-03 pinned all tasks to respecting core
2026-06-03 added a cutom panic-handler to set the status led to red if panic happens
2026-06-11 changed idle state
2026-06-12 deleted old and unused files and added ducomentation pictures and diagrams
2026-06-16 tried fix v1
2026-06-16 tried fix v2
2026-06-17 fixed IO-Expander issues with incorrect initialization and automatic reset
2026-06-17 fixed race-condition in gamelogic
2026-06-17 moved LittleFS Initialization into main
2026-06-17 added missing volatile keywords
2026-06-17 added out-of-bound checks
2026-06-17 added improved i2c check
2026-06-17 added self-healing highscore-manager
2026-06-17 prohibit the first targets to be the start-buttons
2026-06-17 fixed volatile++ being deprecated warning
2026-06-17 webserver nearly finished working
2026-06-17 readded custom panic handler
2026-06-17 added website selection of newest highscore
2026-06-17 added improved i2c errer handling
2026-06-17 fixed error with improved i2c error handling
2026-06-17 secured highscore at gameover
2026-06-17 changed Website to automatically open name-field for most recent highscore
2026-06-17 newOptions
2026-06-17 fixed bugs
2026-06-17 new esp config
2026-06-17 added game start logging
2026-06-17 added i2c-bus recovery at setup
2026-06-17 deleted KiCad history subrepo
2026-06-18 changed gitignore (no Cache)
2026-06-18 changed colors and highscore reset
2026-06-18 added Start state and traffic light animation
2026-06-18 added stability changes
2026-06-18 added more Weblogging and refactored Logging messages
2026-06-18 changed animation color
2026-06-18 deleted unneccessary logging
2026-06-18 changed Landing Page
2026-06-18 fixed multiple occurence of logs
2026-06-19 added README
